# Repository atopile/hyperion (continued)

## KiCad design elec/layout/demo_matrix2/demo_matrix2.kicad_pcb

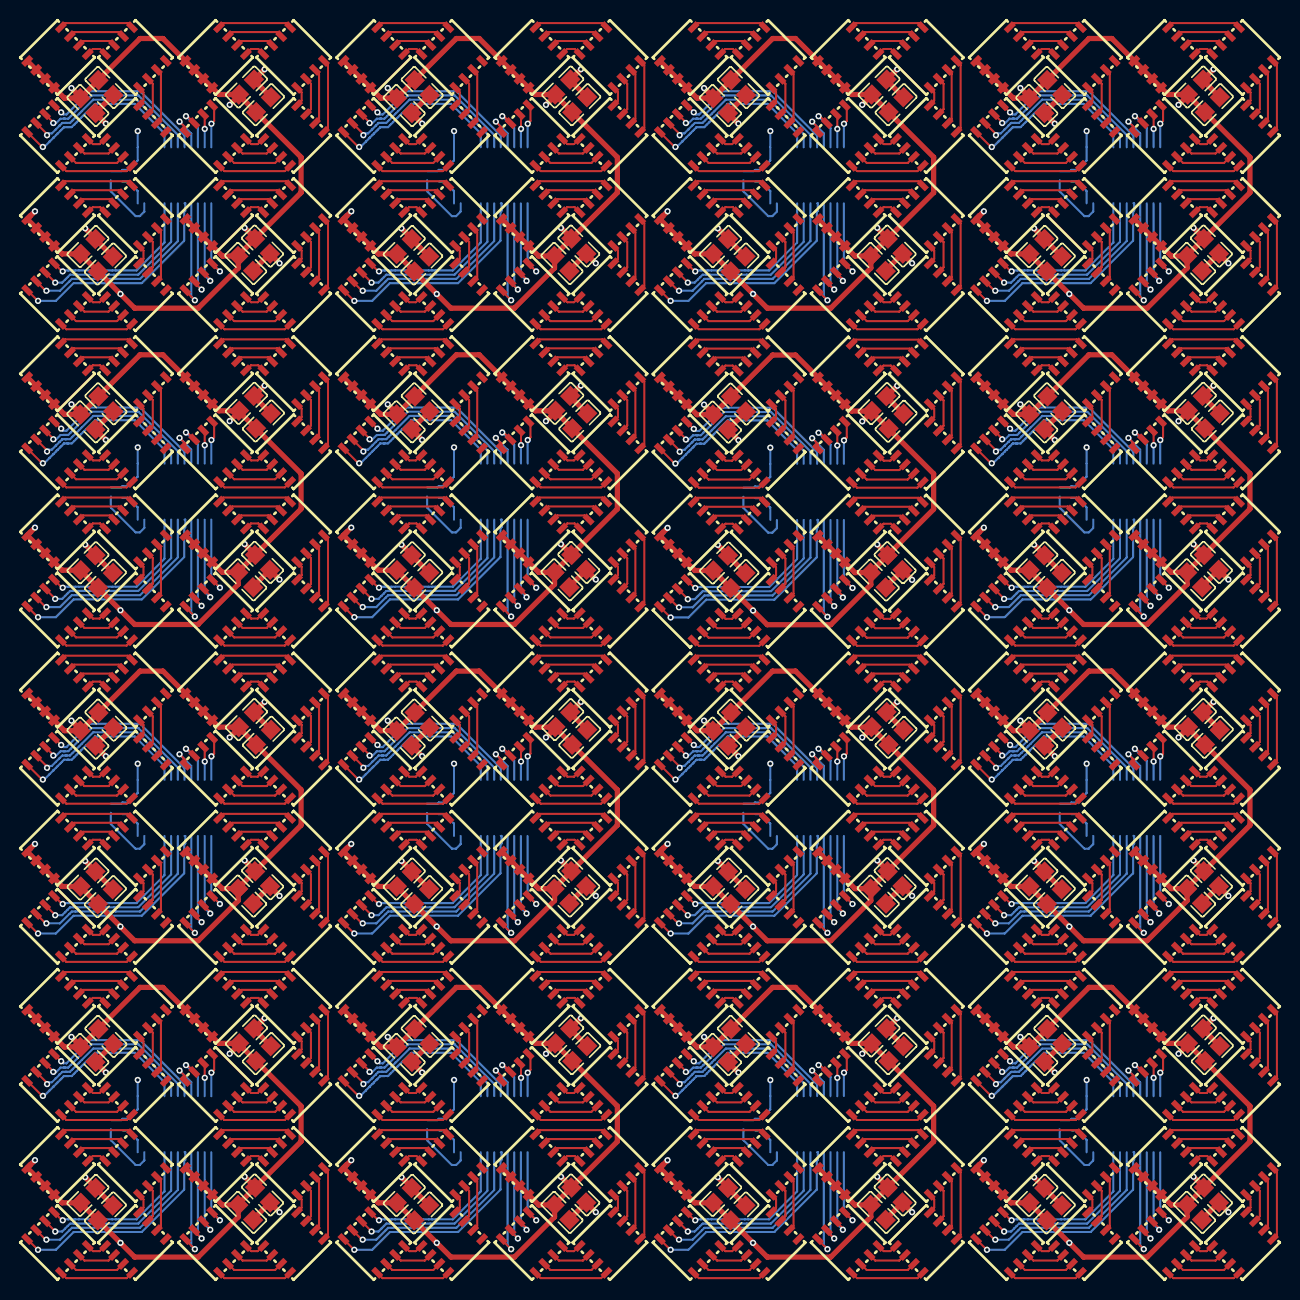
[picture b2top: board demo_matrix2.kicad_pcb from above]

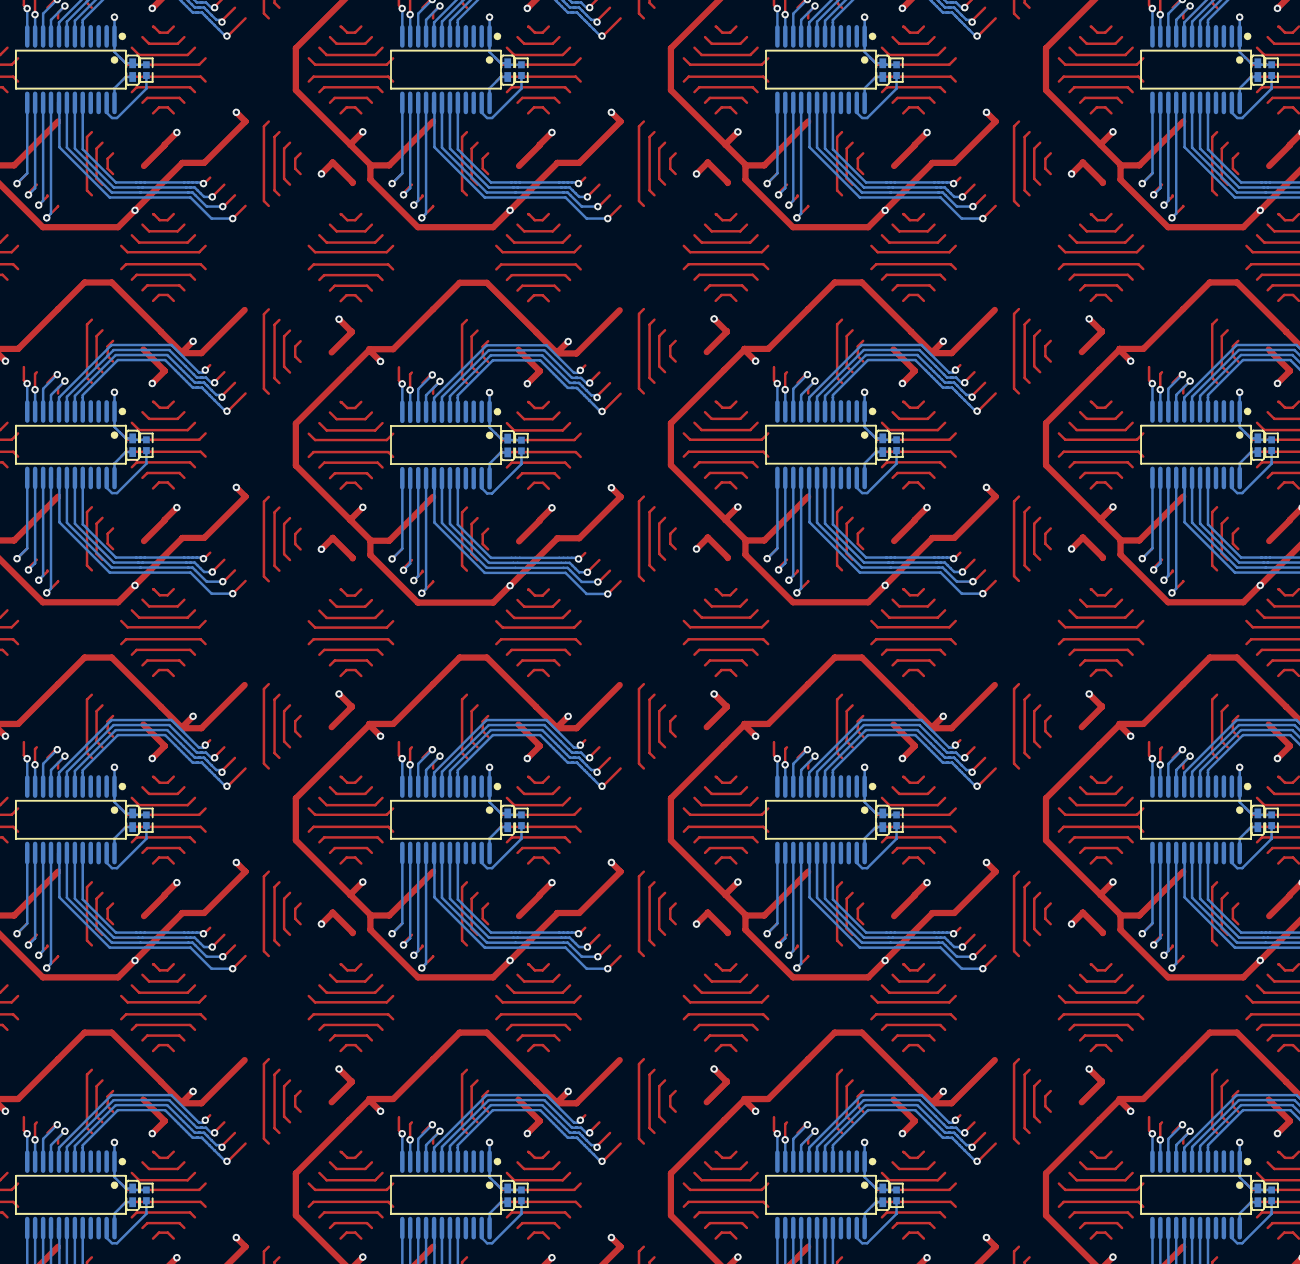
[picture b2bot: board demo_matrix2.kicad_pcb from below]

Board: 2 copper layers, 496 parts (48 on the bottom side), 1104 nets.

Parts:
C1, C2, C3, C4, C5, C6, C7, C8, C10, C11, C12, C13, C14, C15, C16, C17, C19, C20, C21, C22, C23, C24, C25, C26, C28, C29, C30, C31, C32, C33, C34, C35, C37, C38, C39, C40, C41, C42, C43, C44, C46, C47, C48, C49, C50, C51, C52, C53, C55, C56, C57, C58, C59, C60, C61, C62, C64, C65, C66, C67, C68, C69, C70, C71, C73, C74, C75, C76, C77, C78, C79, C80, C82, C83, C84, C85, C86, C87, C88, C89, C91, C92, C93, C94, C95, C96, C97, C98, C100, C101, C102, C103, C104, C105, C106, C107, C109, C110, C111, C112, C113, C114, C115, C116, C118, C119, C120, C121, C122, C123, C124, C125, C127, C128, C129, C130, C131, C132, C133, C134, C136, C137, C138, C139, C140, C141, C142, C143: 10µF ±10% 25V X5R; C0805
C9, C18, C27, C36, C45, C54, C63, C72, C81, C90, C99, C108, C117, C126, C135, C144: 100nF ±10% 16V X7R; C0402
LED1, LED2, LED3, LED4, LED5, LED6, LED7, LED8, LED9, LED10, LED11, LED12, LED13, LED14, LED15, LED16, LED17, LED18, LED19, LED20, LED21, LED22, LED23, LED24, LED25, LED26, LED27, LED28, LED29, LED30, LED31, LED32, LED33, LED34, LED35, LED36, LED37, LED38, LED39, LED40, LED41, LED42, LED43, LED44, LED45, LED46, LED47, LED48, LED49, LED50, LED51, LED52, LED53, LED54, LED55, LED56, LED57, LED58, LED59, LED60, LED61, LED62, LED63, LED64, LED65, LED66, LED67, LED68, LED69, LED70, LED71, LED72, LED73, LED74, LED75, LED76, LED77, LED78, LED79, LED80, LED81, LED82, LED83, LED84, LED85, LED86, LED87, LED88, LED89, LED90, LED91, LED92, LED93, LED94, LED95, LED96, LED97, LED98, LED99, LED100, LED101, LED102, LED103, LED104, LED105, LED106, LED107, LED108, LED109, LED110, LED111, LED112, LED113, LED114, LED115, LED116, LED117, LED118, LED119, LED120, LED121, LED122, LED123, LED124, LED125, LED126, LED127, LED128, LED129, LED130, LED131, LED132, LED133, LED134, LED135, LED136, LED137, LED138, LED139, LED140, LED141, LED142, LED143, LED144, LED145, LED146, LED147, LED148, LED149, LED150, LED151, LED152, LED153, LED154, LED155, LED156, LED157, LED158, LED159, LED160, LED161, LED162, LED163, LED164, LED165, LED166, LED167, LED168, LED169, LED170, LED171, LED172, LED173, LED174, LED175, LED176, LED177, LED178, LED179, LED180, LED181, LED182, LED183, LED184, LED185, LED186, LED187, LED188, LED189, LED190, LED191, LED192, LED193, LED194, LED195, LED196, LED197, LED198, LED199, LED200, LED201, LED202, LED203, LED204, LED205, LED206, LED207, LED208, LED209, LED210, LED211, LED212, LED213, LED214, LED215, LED216, LED217, LED218, LED219, LED220, LED221, LED222, LED223, LED224, LED225, LED226, LED227, LED228, LED229, LED230, LED231, LED232, LED233, LED234, LED235, LED236, LED237, LED238, LED239, LED240, LED241, LED242, LED243, LED244, LED245, LED246, LED247, LED248, LED249, LED250, LED251, LED252, LED253, LED254, LED255, LED256: LED-SMD_8P-L5.0-W5.0-P1.20_HL-5050RGBW-S1-A27
R1, R2, R3, R4, R5, R6, R7, R8, R9, R10, R11, R12, R13, R14, R15, R16: 10kΩ ±1% 62.5mW; R0402
U1, U6, U11, U16, U21, U26, U31, U36, U41, U46, U51, U56, U61, U66, U71, U76: SSOP-24_L8.8-W4.0-P0.64-LS6.2-BL
U2, U3, U4, U5, U7, U8, U9, U10, U12, U13, U14, U15, U17, U18, U19, U20, U22, U23, U24, U25, U27, U28, U29, U30, U32, U33, U34, U35, U37, U38, U39, U40, U42, U43, U44, U45, U47, U48, U49, U50, U52, U53, U54, U55, U57, U58, U59, U60, U62, U63, U64, U65, U67, U68, U69, U70, U72, U73, U74, U75, U77, U78, U79, U80: pixel15

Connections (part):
clusters[0]-REXT: R1.1, U1.23
clusters[1]-REXT: R2.1, U6.23
clusters[2]-REXT: R3.1, U11.23
clusters[3]-REXT: R4.1, U16.23
clusters[4]-REXT: R5.1, U21.23
clusters[5]-REXT: R6.1, U26.23
clusters[6]-REXT: R7.1, U31.23
clusters[7]-REXT: R8.1, U36.23
clusters[8]-REXT: R9.1, U41.23
clusters[9]-REXT: R10.1, U46.23
clusters[10]-REXT: R11.1, U51.23
clusters[11]-REXT: R12.1, U56.23
clusters[12]-REXT: R13.1, U61.23
clusters[13]-REXT: R14.1, U66.23
clusters[14]-REXT: R15.1, U71.23
clusters[15]-REXT: R16.1, U76.23
decoupling_capacitors[7]-power_shim-GND-0: C1.2, C2.2, C3.2, C4.2, C5.2, C6.2, C7.2, C8.2
decoupling_capacitors[7]-power_shim-GND-1: C91.2, C92.2, C93.2, C94.2, C95.2, C96.2, C97.2, C98.2
decoupling_capacitors[7]-power_shim-GND-2: C100.2, C101.2, C102.2, C103.2, C104.2, C105.2, C106.2, C107.2
decoupling_capacitors[7]-power_shim-GND-3: C109.2, C110.2, C111.2, C112.2, C113.2, C114.2, C115.2, C116.2
decoupling_capacitors[7]-power_shim-GND-4: C118.2, C119.2, C120.2, C121.2, C122.2, C123.2, C124.2, C125.2
decoupling_capacitors[7]-power_shim-GND-5: C127.2, C128.2, C129.2, C130.2, C131.2, C132.2, C133.2, C134.2
decoupling_capacitors[7]-power_shim-GND-6: C136.2, C137.2, C138.2, C139.2, C140.2, C141.2, C142.2, C143.2
decoupling_capacitors[7]-power_shim-GND-7: C10.2, C11.2, C12.2, C13.2, C14.2, C15.2, C16.2, C17.2
decoupling_capacitors[7]-power_shim-GND-8: C19.2, C20.2, C21.2, C22.2, C23.2, C24.2, C25.2, C26.2
decoupling_capacitors[7]-power_shim-GND-9: C28.2, C29.2, C30.2, C31.2, C32.2, C33.2, C34.2, C35.2
decoupling_capacitors[7]-power_shim-GND-10: C37.2, C38.2, C39.2, C40.2, C41.2, C42.2, C43.2, C44.2
decoupling_capacitors[7]-power_shim-GND-11: C46.2, C47.2, C48.2, C49.2, C50.2, C51.2, C52.2, C53.2
decoupling_capacitors[7]-power_shim-GND-12: C55.2, C56.2, C57.2, C58.2, C59.2, C60.2, C61.2, C62.2
decoupling_capacitors[7]-power_shim-GND-13: C64.2, C65.2, C66.2, C67.2, C68.2, C69.2, C70.2, C71.2
decoupling_capacitors[7]-power_shim-GND-14: C73.2, C74.2, C75.2, C76.2, C77.2, C78.2, C79.2, C80.2
decoupling_capacitors[7]-power_shim-GND-15: C82.2, C83.2, C84.2, C85.2, C86.2, C87.2, C88.2, C89.2
decoupling_capacitors[7]-power_shim-VCC-0: C1.1, C2.1, C3.1, C4.1, C5.1, C6.1, C7.1, C8.1, LED1.2, LED1.4, LED1.6, LED1.8, LED5.2, LED5.4, LED5.6, LED5.8, LED9.2, LED9.4, LED9.6, LED9.8, LED13.2, LED13.4, LED13.6, LED13.8
decoupling_capacitors[7]-power_shim-VCC-1: C91.1, C92.1, C93.1, C94.1, C95.1, C96.1, C97.1, C98.1, LED161.2, LED161.4, LED161.6, LED161.8, LED165.2, LED165.4, LED165.6, LED165.8, LED169.2, LED169.4, LED169.6, LED169.8, LED173.2, LED173.4, LED173.6, LED173.8
decoupling_capacitors[7]-power_shim-VCC-2: C100.1, C101.1, C102.1, C103.1, C104.1, C105.1, C106.1, C107.1, LED177.2, LED177.4, LED177.6, LED177.8, LED181.2, LED181.4, LED181.6, LED181.8, LED185.2, LED185.4, LED185.6, LED185.8, LED189.2, LED189.4, LED189.6, LED189.8
decoupling_capacitors[7]-power_shim-VCC-3: C109.1, C110.1, C111.1, C112.1, C113.1, C114.1, C115.1, C116.1, LED193.2, LED193.4, LED193.6, LED193.8, LED197.2, LED197.4, LED197.6, LED197.8, LED201.2, LED201.4, LED201.6, LED201.8, LED205.2, LED205.4, LED205.6, LED205.8
decoupling_capacitors[7]-power_shim-VCC-4: C118.1, C119.1, C120.1, C121.1, C122.1, C123.1, C124.1, C125.1, LED209.2, LED209.4, LED209.6, LED209.8, LED213.2, LED213.4, LED213.6, LED213.8, LED217.2, LED217.4, LED217.6, LED217.8, LED221.2, LED221.4, LED221.6, LED221.8
decoupling_capacitors[7]-power_shim-VCC-5: C127.1, C128.1, C129.1, C130.1, C131.1, C132.1, C133.1, C134.1, LED225.2, LED225.4, LED225.6, LED225.8, LED229.2, LED229.4, LED229.6, LED229.8, LED233.2, LED233.4, LED233.6, LED233.8, LED237.2, LED237.4, LED237.6, LED237.8
decoupling_capacitors[7]-power_shim-VCC-6: C136.1, C137.1, C138.1, C139.1, C140.1, C141.1, C142.1, C143.1, LED241.2, LED241.4, LED241.6, LED241.8, LED245.2, LED245.4, LED245.6, LED245.8, LED249.2, LED249.4, LED249.6, LED249.8, LED253.2, LED253.4, LED253.6, LED253.8
decoupling_capacitors[7]-power_shim-VCC-7: C10.1, C11.1, C12.1, C13.1, C14.1, C15.1, C16.1, C17.1, LED17.2, LED17.4, LED17.6, LED17.8, LED21.2, LED21.4, LED21.6, LED21.8, LED25.2, LED25.4, LED25.6, LED25.8, LED29.2, LED29.4, LED29.6, LED29.8
decoupling_capacitors[7]-power_shim-VCC-8: C19.1, C20.1, C21.1, C22.1, C23.1, C24.1, C25.1, C26.1, LED33.2, LED33.4, LED33.6, LED33.8, LED37.2, LED37.4, LED37.6, LED37.8, LED41.2, LED41.4, LED41.6, LED41.8, LED45.2, LED45.4, LED45.6, LED45.8
decoupling_capacitors[7]-power_shim-VCC-9: C28.1, C29.1, C30.1, C31.1, C32.1, C33.1, C34.1, C35.1, LED49.2, LED49.4, LED49.6, LED49.8, LED53.2, LED53.4, LED53.6, LED53.8, LED57.2, LED57.4, LED57.6, LED57.8, LED61.2, LED61.4, LED61.6, LED61.8
decoupling_capacitors[7]-power_shim-VCC-10: C37.1, C38.1, C39.1, C40.1, C41.1, C42.1, C43.1, C44.1, LED65.2, LED65.4, LED65.6, LED65.8, LED69.2, LED69.4, LED69.6, LED69.8, LED73.2, LED73.4, LED73.6, LED73.8, LED77.2, LED77.4, LED77.6, LED77.8
decoupling_capacitors[7]-power_shim-VCC-11: C46.1, C47.1, C48.1, C49.1, C50.1, C51.1, C52.1, C53.1, LED81.2, LED81.4, LED81.6, LED81.8, LED85.2, LED85.4, LED85.6, LED85.8, LED89.2, LED89.4, LED89.6, LED89.8, LED93.2, LED93.4, LED93.6, LED93.8
decoupling_capacitors[7]-power_shim-VCC-12: C55.1, C56.1, C57.1, C58.1, C59.1, C60.1, C61.1, C62.1, LED97.2, LED97.4, LED97.6, LED97.8, LED101.2, LED101.4, LED101.6, LED101.8, LED105.2, LED105.4, LED105.6, LED105.8, LED109.2, LED109.4, LED109.6, LED109.8
decoupling_capacitors[7]-power_shim-VCC-13: C64.1, C65.1, C66.1, C67.1, C68.1, C69.1, C70.1, C71.1, LED113.2, LED113.4, LED113.6, LED113.8, LED117.2, LED117.4, LED117.6, LED117.8, LED121.2, LED121.4, LED121.6, LED121.8, LED125.2, LED125.4, LED125.6, LED125.8
decoupling_capacitors[7]-power_shim-VCC-14: C73.1, C74.1, C75.1, C76.1, C77.1, C78.1, C79.1, C80.1, LED129.2, LED129.4, LED129.6, LED129.8, LED133.2, LED133.4, LED133.6, LED133.8, LED137.2, LED137.4, LED137.6, LED137.8, LED141.2, LED141.4, LED141.6, LED141.8
decoupling_capacitors[7]-power_shim-VCC-15: C82.1, C83.1, C84.1, C85.1, C86.1, C87.1, C88.1, C89.1, LED145.2, LED145.4, LED145.6, LED145.8, LED149.2, LED149.4, LED149.6, LED149.8, LED153.2, LED153.4, LED153.6, LED153.8, LED157.2, LED157.4, LED157.6, LED157.8
driver-power-GND-0: C9.2, R1.2, U1.1
driver-power-GND-1: C99.2, R11.2, U51.1
driver-power-GND-2: C108.2, R12.2, U56.1
driver-power-GND-3: C117.2, R13.2, U61.1
driver-power-GND-4: C126.2, R14.2, U66.1
driver-power-GND-5: C135.2, R15.2, U71.1
driver-power-GND-6: C144.2, R16.2, U76.1
driver-power-GND-7: C18.2, R2.2, U6.1
driver-power-GND-8: C27.2, R3.2, U11.1
driver-power-GND-9: C36.2, R4.2, U16.1
driver-power-GND-10: C45.2, R5.2, U21.1
driver-power-GND-11: C54.2, R6.2, U26.1
driver-power-GND-12: C63.2, R7.2, U31.1
driver-power-GND-13: C72.2, R8.2, U36.1
driver-power-GND-14: C81.2, R9.2, U41.1
driver-power-GND-15: C90.2, R10.2, U46.1
driver-power-VCC-0: C9.1, U1.24
driver-power-VCC-1: C99.1, U51.24
driver-power-VCC-2: C108.1, U56.24
driver-power-VCC-3: C117.1, U61.24
driver-power-VCC-4: C126.1, U66.24
driver-power-VCC-5: C135.1, U71.24
driver-power-VCC-6: C144.1, U76.24
driver-power-VCC-7: C18.1, U6.24
driver-power-VCC-8: C27.1, U11.24
driver-power-VCC-9: C36.1, U16.24
driver-power-VCC-10: C45.1, U21.24
driver-power-VCC-11: C54.1, U26.24
driver-power-VCC-12: C63.1, U31.24
driver-power-VCC-13: C72.1, U36.24
driver-power-VCC-14: C81.1, U41.24
driver-power-VCC-15: C90.1, U46.24
rgbs[1]-anodes-anode-0: LED1.3, LED2.4
rgbs[1]-anodes-anode-1: LED1.1, LED2.2
rgbs[1]-anodes-anode-2: LED1.5, LED2.6
rgbs[1]-anodes-anode-3: LED1.7, LED2.8
rgbs[1]-anodes-anode-4: LED5.3, LED6.4
rgbs[1]-anodes-anode-5: LED5.1, LED6.2
rgbs[1]-anodes-anode-6: LED5.5, LED6.6
rgbs[1]-anodes-anode-7: LED5.7, LED6.8
rgbs[1]-anodes-anode-8: LED9.3, LED10.4
rgbs[1]-anodes-anode-9: LED9.1, LED10.2
rgbs[1]-anodes-anode-10: LED9.5, LED10.6
rgbs[1]-anodes-anode-11: LED9.7, LED10.8
rgbs[1]-anodes-anode-12: LED13.3, LED14.4
rgbs[1]-anodes-anode-13: LED13.1, LED14.2
rgbs[1]-anodes-anode-14: LED13.5, LED14.6
rgbs[1]-anodes-anode-15: LED13.7, LED14.8
rgbs[1]-anodes-anode-16: LED161.3, LED162.4
rgbs[1]-anodes-anode-17: LED161.1, LED162.2
rgbs[1]-anodes-anode-18: LED161.5, LED162.6
rgbs[1]-anodes-anode-19: LED161.7, LED162.8
rgbs[1]-anodes-anode-20: LED165.3, LED166.4
rgbs[1]-anodes-anode-21: LED165.1, LED166.2
rgbs[1]-anodes-anode-22: LED165.5, LED166.6
rgbs[1]-anodes-anode-23: LED165.7, LED166.8
rgbs[1]-anodes-anode-24: LED169.3, LED170.4
rgbs[1]-anodes-anode-25: LED169.1, LED170.2
rgbs[1]-anodes-anode-26: LED169.5, LED170.6
rgbs[1]-anodes-anode-27: LED169.7, LED170.8
rgbs[1]-anodes-anode-28: LED173.3, LED174.4
rgbs[1]-anodes-anode-29: LED173.1, LED174.2
rgbs[1]-anodes-anode-30: LED173.5, LED174.6
rgbs[1]-anodes-anode-31: LED173.7, LED174.8
rgbs[1]-anodes-anode-32: LED177.3, LED178.4
rgbs[1]-anodes-anode-33: LED177.1, LED178.2
rgbs[1]-anodes-anode-34: LED177.5, LED178.6
rgbs[1]-anodes-anode-35: LED177.7, LED178.8
rgbs[1]-anodes-anode-36: LED181.3, LED182.4
rgbs[1]-anodes-anode-37: LED181.1, LED182.2
rgbs[1]-anodes-anode-38: LED181.5, LED182.6
rgbs[1]-anodes-anode-39: LED181.7, LED182.8
rgbs[1]-anodes-anode-40: LED185.3, LED186.4
rgbs[1]-anodes-anode-41: LED185.1, LED186.2
rgbs[1]-anodes-anode-42: LED185.5, LED186.6
rgbs[1]-anodes-anode-43: LED185.7, LED186.8
rgbs[1]-anodes-anode-44: LED189.3, LED190.4
rgbs[1]-anodes-anode-45: LED189.1, LED190.2
rgbs[1]-anodes-anode-46: LED189.5, LED190.6
rgbs[1]-anodes-anode-47: LED189.7, LED190.8
rgbs[1]-anodes-anode-48: LED193.3, LED194.4
rgbs[1]-anodes-anode-49: LED193.1, LED194.2
rgbs[1]-anodes-anode-50: LED193.5, LED194.6
rgbs[1]-anodes-anode-51: LED193.7, LED194.8
rgbs[1]-anodes-anode-52: LED197.3, LED198.4
rgbs[1]-anodes-anode-53: LED197.1, LED198.2
rgbs[1]-anodes-anode-54: LED197.5, LED198.6
rgbs[1]-anodes-anode-55: LED197.7, LED198.8
rgbs[1]-anodes-anode-56: LED201.3, LED202.4
rgbs[1]-anodes-anode-57: LED201.1, LED202.2
rgbs[1]-anodes-anode-58: LED201.5, LED202.6
rgbs[1]-anodes-anode-59: LED201.7, LED202.8
rgbs[1]-anodes-anode-60: LED205.3, LED206.4
rgbs[1]-anodes-anode-61: LED205.1, LED206.2
rgbs[1]-anodes-anode-62: LED205.5, LED206.6
rgbs[1]-anodes-anode-63: LED205.7, LED206.8
rgbs[1]-anodes-anode-64: LED209.3, LED210.4
rgbs[1]-anodes-anode-65: LED209.1, LED210.2
rgbs[1]-anodes-anode-66: LED209.5, LED210.6
rgbs[1]-anodes-anode-67: LED209.7, LED210.8
rgbs[1]-anodes-anode-68: LED213.3, LED214.4
rgbs[1]-anodes-anode-69: LED213.1, LED214.2
rgbs[1]-anodes-anode-70: LED213.5, LED214.6
rgbs[1]-anodes-anode-71: LED213.7, LED214.8
rgbs[1]-anodes-anode-72: LED217.3, LED218.4
rgbs[1]-anodes-anode-73: LED217.1, LED218.2
rgbs[1]-anodes-anode-74: LED217.5, LED218.6
rgbs[1]-anodes-anode-75: LED217.7, LED218.8
rgbs[1]-anodes-anode-76: LED221.3, LED222.4
rgbs[1]-anodes-anode-77: LED221.1, LED222.2
rgbs[1]-anodes-anode-78: LED221.5, LED222.6
rgbs[1]-anodes-anode-79: LED221.7, LED222.8
rgbs[1]-anodes-anode-80: LED225.3, LED226.4
rgbs[1]-anodes-anode-81: LED225.1, LED226.2
rgbs[1]-anodes-anode-82: LED225.5, LED226.6
rgbs[1]-anodes-anode-83: LED225.7, LED226.8
rgbs[1]-anodes-anode-84: LED229.3, LED230.4
rgbs[1]-anodes-anode-85: LED229.1, LED230.2
rgbs[1]-anodes-anode-86: LED229.5, LED230.6
rgbs[1]-anodes-anode-87: LED229.7, LED230.8
rgbs[1]-anodes-anode-88: LED233.3, LED234.4
rgbs[1]-anodes-anode-89: LED233.1, LED234.2
rgbs[1]-anodes-anode-90: LED233.5, LED234.6
rgbs[1]-anodes-anode-91: LED233.7, LED234.8
rgbs[1]-anodes-anode-92: LED237.3, LED238.4
rgbs[1]-anodes-anode-93: LED237.1, LED238.2
rgbs[1]-anodes-anode-94: LED237.5, LED238.6
rgbs[1]-anodes-anode-95: LED237.7, LED238.8
rgbs[1]-anodes-anode-96: LED241.3, LED242.4
rgbs[1]-anodes-anode-97: LED241.1, LED242.2
rgbs[1]-anodes-anode-98: LED241.5, LED242.6
rgbs[1]-anodes-anode-99: LED241.7, LED242.8
rgbs[1]-anodes-anode-100: LED245.3, LED246.4
rgbs[1]-anodes-anode-101: LED245.1, LED246.2
rgbs[1]-anodes-anode-102: LED245.5, LED246.6
rgbs[1]-anodes-anode-103: LED245.7, LED246.8
rgbs[1]-anodes-anode-104: LED249.3, LED250.4
rgbs[1]-anodes-anode-105: LED249.1, LED250.2
rgbs[1]-anodes-anode-106: LED249.5, LED250.6
rgbs[1]-anodes-anode-107: LED249.7, LED250.8
rgbs[1]-anodes-anode-108: LED253.3, LED254.4
rgbs[1]-anodes-anode-109: LED253.1, LED254.2
rgbs[1]-anodes-anode-110: LED253.5, LED254.6
rgbs[1]-anodes-anode-111: LED253.7, LED254.8
rgbs[1]-anodes-anode-112: LED17.3, LED18.4
rgbs[1]-anodes-anode-113: LED17.1, LED18.2
rgbs[1]-anodes-anode-114: LED17.5, LED18.6
rgbs[1]-anodes-anode-115: LED17.7, LED18.8
rgbs[1]-anodes-anode-116: LED21.3, LED22.4
rgbs[1]-anodes-anode-117: LED21.1, LED22.2
rgbs[1]-anodes-anode-118: LED21.5, LED22.6
rgbs[1]-anodes-anode-119: LED21.7, LED22.8
rgbs[1]-anodes-anode-120: LED25.3, LED26.4
rgbs[1]-anodes-anode-121: LED25.1, LED26.2
rgbs[1]-anodes-anode-122: LED25.5, LED26.6
rgbs[1]-anodes-anode-123: LED25.7, LED26.8
rgbs[1]-anodes-anode-124: LED29.3, LED30.4
rgbs[1]-anodes-anode-125: LED29.1, LED30.2
rgbs[1]-anodes-anode-126: LED29.5, LED30.6
rgbs[1]-anodes-anode-127: LED29.7, LED30.8
rgbs[1]-anodes-anode-128: LED33.3, LED34.4
rgbs[1]-anodes-anode-129: LED33.1, LED34.2
rgbs[1]-anodes-anode-130: LED33.5, LED34.6
rgbs[1]-anodes-anode-131: LED33.7, LED34.8
rgbs[1]-anodes-anode-132: LED37.3, LED38.4
rgbs[1]-anodes-anode-133: LED37.1, LED38.2
rgbs[1]-anodes-anode-134: LED37.5, LED38.6
rgbs[1]-anodes-anode-135: LED37.7, LED38.8
rgbs[1]-anodes-anode-136: LED41.3, LED42.4
rgbs[1]-anodes-anode-137: LED41.1, LED42.2
rgbs[1]-anodes-anode-138: LED41.5, LED42.6
rgbs[1]-anodes-anode-139: LED41.7, LED42.8
rgbs[1]-anodes-anode-140: LED45.3, LED46.4
rgbs[1]-anodes-anode-141: LED45.1, LED46.2
rgbs[1]-anodes-anode-142: LED45.5, LED46.6
rgbs[1]-anodes-anode-143: LED45.7, LED46.8
rgbs[1]-anodes-anode-144: LED49.3, LED50.4
rgbs[1]-anodes-anode-145: LED49.1, LED50.2
rgbs[1]-anodes-anode-146: LED49.5, LED50.6
rgbs[1]-anodes-anode-147: LED49.7, LED50.8
rgbs[1]-anodes-anode-148: LED53.3, LED54.4
rgbs[1]-anodes-anode-149: LED53.1, LED54.2
rgbs[1]-anodes-anode-150: LED53.5, LED54.6
rgbs[1]-anodes-anode-151: LED53.7, LED54.8
rgbs[1]-anodes-anode-152: LED57.3, LED58.4
rgbs[1]-anodes-anode-153: LED57.1, LED58.2
rgbs[1]-anodes-anode-154: LED57.5, LED58.6
rgbs[1]-anodes-anode-155: LED57.7, LED58.8
rgbs[1]-anodes-anode-156: LED61.3, LED62.4
rgbs[1]-anodes-anode-157: LED61.1, LED62.2
rgbs[1]-anodes-anode-158: LED61.5, LED62.6
rgbs[1]-anodes-anode-159: LED61.7, LED62.8
rgbs[1]-anodes-anode-160: LED65.3, LED66.4
rgbs[1]-anodes-anode-161: LED65.1, LED66.2
rgbs[1]-anodes-anode-162: LED65.5, LED66.6
rgbs[1]-anodes-anode-163: LED65.7, LED66.8
rgbs[1]-anodes-anode-164: LED69.3, LED70.4
rgbs[1]-anodes-anode-165: LED69.1, LED70.2
rgbs[1]-anodes-anode-166: LED69.5, LED70.6
rgbs[1]-anodes-anode-167: LED69.7, LED70.8
rgbs[1]-anodes-anode-168: LED73.3, LED74.4
rgbs[1]-anodes-anode-169: LED73.1, LED74.2
rgbs[1]-anodes-anode-170: LED73.5, LED74.6
rgbs[1]-anodes-anode-171: LED73.7, LED74.8
rgbs[1]-anodes-anode-172: LED77.3, LED78.4
rgbs[1]-anodes-anode-173: LED77.1, LED78.2
rgbs[1]-anodes-anode-174: LED77.5, LED78.6
rgbs[1]-anodes-anode-175: LED77.7, LED78.8
rgbs[1]-anodes-anode-176: LED81.3, LED82.4
rgbs[1]-anodes-anode-177: LED81.1, LED82.2
rgbs[1]-anodes-anode-178: LED81.5, LED82.6
rgbs[1]-anodes-anode-179: LED81.7, LED82.8
rgbs[1]-anodes-anode-180: LED85.3, LED86.4
rgbs[1]-anodes-anode-181: LED85.1, LED86.2
rgbs[1]-anodes-anode-182: LED85.5, LED86.6
rgbs[1]-anodes-anode-183: LED85.7, LED86.8
rgbs[1]-anodes-anode-184: LED89.3, LED90.4
rgbs[1]-anodes-anode-185: LED89.1, LED90.2
rgbs[1]-anodes-anode-186: LED89.5, LED90.6
rgbs[1]-anodes-anode-187: LED89.7, LED90.8
rgbs[1]-anodes-anode-188: LED93.3, LED94.4
rgbs[1]-anodes-anode-189: LED93.1, LED94.2
rgbs[1]-anodes-anode-190: LED93.5, LED94.6
rgbs[1]-anodes-anode-191: LED93.7, LED94.8
rgbs[1]-anodes-anode-192: LED97.3, LED98.4
rgbs[1]-anodes-anode-193: LED97.1, LED98.2
rgbs[1]-anodes-anode-194: LED97.5, LED98.6
rgbs[1]-anodes-anode-195: LED97.7, LED98.8
rgbs[1]-anodes-anode-196: LED101.3, LED102.4
rgbs[1]-anodes-anode-197: LED101.1, LED102.2
rgbs[1]-anodes-anode-198: LED101.5, LED102.6
rgbs[1]-anodes-anode-199: LED101.7, LED102.8
rgbs[1]-anodes-anode-200: LED105.3, LED106.4
rgbs[1]-anodes-anode-201: LED105.1, LED106.2
rgbs[1]-anodes-anode-202: LED105.5, LED106.6
rgbs[1]-anodes-anode-203: LED105.7, LED106.8
rgbs[1]-anodes-anode-204: LED109.3, LED110.4
rgbs[1]-anodes-anode-205: LED109.1, LED110.2
rgbs[1]-anodes-anode-206: LED109.5, LED110.6
rgbs[1]-anodes-anode-207: LED109.7, LED110.8
rgbs[1]-anodes-anode-208: LED113.3, LED114.4
rgbs[1]-anodes-anode-209: LED113.1, LED114.2
rgbs[1]-anodes-anode-210: LED113.5, LED114.6
rgbs[1]-anodes-anode-211: LED113.7, LED114.8
rgbs[1]-anodes-anode-212: LED117.3, LED118.4
rgbs[1]-anodes-anode-213: LED117.1, LED118.2
rgbs[1]-anodes-anode-214: LED117.5, LED118.6
rgbs[1]-anodes-anode-215: LED117.7, LED118.8
rgbs[1]-anodes-anode-216: LED121.3, LED122.4
rgbs[1]-anodes-anode-217: LED121.1, LED122.2
rgbs[1]-anodes-anode-218: LED121.5, LED122.6
rgbs[1]-anodes-anode-219: LED121.7, LED122.8
rgbs[1]-anodes-anode-220: LED125.3, LED126.4
rgbs[1]-anodes-anode-221: LED125.1, LED126.2
rgbs[1]-anodes-anode-222: LED125.5, LED126.6
rgbs[1]-anodes-anode-223: LED125.7, LED126.8
rgbs[1]-anodes-anode-224: LED129.3, LED130.4
rgbs[1]-anodes-anode-225: LED129.1, LED130.2
rgbs[1]-anodes-anode-226: LED129.5, LED130.6
rgbs[1]-anodes-anode-227: LED129.7, LED130.8
rgbs[1]-anodes-anode-228: LED133.3, LED134.4
rgbs[1]-anodes-anode-229: LED133.1, LED134.2
rgbs[1]-anodes-anode-230: LED133.5, LED134.6
rgbs[1]-anodes-anode-231: LED133.7, LED134.8
rgbs[1]-anodes-anode-232: LED137.3, LED138.4
rgbs[1]-anodes-anode-233: LED137.1, LED138.2
rgbs[1]-anodes-anode-234: LED137.5, LED138.6
rgbs[1]-anodes-anode-235: LED137.7, LED138.8
rgbs[1]-anodes-anode-236: LED141.3, LED142.4
rgbs[1]-anodes-anode-237: LED141.1, LED142.2
rgbs[1]-anodes-anode-238: LED141.5, LED142.6
rgbs[1]-anodes-anode-239: LED141.7, LED142.8
rgbs[1]-anodes-anode-240: LED145.3, LED146.4
rgbs[1]-anodes-anode-241: LED145.1, LED146.2
rgbs[1]-anodes-anode-242: LED145.5, LED146.6
rgbs[1]-anodes-anode-243: LED145.7, LED146.8
rgbs[1]-anodes-anode-244: LED149.3, LED150.4
rgbs[1]-anodes-anode-245: LED149.1, LED150.2
rgbs[1]-anodes-anode-246: LED149.5, LED150.6
rgbs[1]-anodes-anode-247: LED149.7, LED150.8
rgbs[1]-anodes-anode-248: LED153.3, LED154.4
rgbs[1]-anodes-anode-249: LED153.1, LED154.2
rgbs[1]-anodes-anode-250: LED153.5, LED154.6
rgbs[1]-anodes-anode-251: LED153.7, LED154.8
rgbs[1]-anodes-anode-252: LED157.3, LED158.4
rgbs[1]-anodes-anode-253: LED157.1, LED158.2
rgbs[1]-anodes-anode-254: LED157.5, LED158.6
rgbs[1]-anodes-anode-255: LED157.7, LED158.8
rgbs[2]-anodes-anode-0: LED2.3, LED3.4
rgbs[2]-anodes-anode-1: LED2.1, LED3.2
rgbs[2]-anodes-anode-2: LED2.5, LED3.6
rgbs[2]-anodes-anode-3: LED2.7, LED3.8
rgbs[2]-anodes-anode-4: LED6.3, LED7.4
rgbs[2]-anodes-anode-5: LED6.1, LED7.2
rgbs[2]-anodes-anode-6: LED6.5, LED7.6
rgbs[2]-anodes-anode-7: LED6.7, LED7.8
rgbs[2]-anodes-anode-8: LED10.3, LED11.4
rgbs[2]-anodes-anode-9: LED10.1, LED11.2
rgbs[2]-anodes-anode-10: LED10.5, LED11.6
rgbs[2]-anodes-anode-11: LED10.7, LED11.8
rgbs[2]-anodes-anode-12: LED14.3, LED15.4
rgbs[2]-anodes-anode-13: LED14.1, LED15.2
rgbs[2]-anodes-anode-14: LED14.5, LED15.6
rgbs[2]-anodes-anode-15: LED14.7, LED15.8
rgbs[2]-anodes-anode-16: LED162.3, LED163.4
rgbs[2]-anodes-anode-17: LED162.1, LED163.2
rgbs[2]-anodes-anode-18: LED162.5, LED163.6
rgbs[2]-anodes-anode-19: LED162.7, LED163.8
rgbs[2]-anodes-anode-20: LED166.3, LED167.4
rgbs[2]-anodes-anode-21: LED166.1, LED167.2
rgbs[2]-anodes-anode-22: LED166.5, LED167.6
rgbs[2]-anodes-anode-23: LED166.7, LED167.8
rgbs[2]-anodes-anode-24: LED170.3, LED171.4
rgbs[2]-anodes-anode-25: LED170.1, LED171.2
rgbs[2]-anodes-anode-26: LED170.5, LED171.6
rgbs[2]-anodes-anode-27: LED170.7, LED171.8
rgbs[2]-anodes-anode-28: LED174.3, LED175.4
rgbs[2]-anodes-anode-29: LED174.1, LED175.2
rgbs[2]-anodes-anode-30: LED174.5, LED175.6
rgbs[2]-anodes-anode-31: LED174.7, LED175.8
rgbs[2]-anodes-anode-32: LED178.3, LED179.4
rgbs[2]-anodes-anode-33: LED178.1, LED179.2
rgbs[2]-anodes-anode-34: LED178.5, LED179.6
rgbs[2]-anodes-anode-35: LED178.7, LED179.8
rgbs[2]-anodes-anode-36: LED182.3, LED183.4
rgbs[2]-anodes-anode-37: LED182.1, LED183.2
rgbs[2]-anodes-anode-38: LED182.5, LED183.6
rgbs[2]-anodes-anode-39: LED182.7, LED183.8
rgbs[2]-anodes-anode-40: LED186.3, LED187.4
rgbs[2]-anodes-anode-41: LED186.1, LED187.2
rgbs[2]-anodes-anode-42: LED186.5, LED187.6
rgbs[2]-anodes-anode-43: LED186.7, LED187.8
rgbs[2]-anodes-anode-44: LED190.3, LED191.4
rgbs[2]-anodes-anode-45: LED190.1, LED191.2
rgbs[2]-anodes-anode-46: LED190.5, LED191.6
rgbs[2]-anodes-anode-47: LED190.7, LED191.8
rgbs[2]-anodes-anode-48: LED194.3, LED195.4
rgbs[2]-anodes-anode-49: LED194.1, LED195.2
rgbs[2]-anodes-anode-50: LED194.5, LED195.6
rgbs[2]-anodes-anode-51: LED194.7, LED195.8
rgbs[2]-anodes-anode-52: LED198.3, LED199.4
rgbs[2]-anodes-anode-53: LED198.1, LED199.2
rgbs[2]-anodes-anode-54: LED198.5, LED199.6
rgbs[2]-anodes-anode-55: LED198.7, LED199.8
rgbs[2]-anodes-anode-56: LED202.3, LED203.4
rgbs[2]-anodes-anode-57: LED202.1, LED203.2
rgbs[2]-anodes-anode-58: LED202.5, LED203.6
rgbs[2]-anodes-anode-59: LED202.7, LED203.8
rgbs[2]-anodes-anode-60: LED206.3, LED207.4
rgbs[2]-anodes-anode-61: LED206.1, LED207.2
rgbs[2]-anodes-anode-62: LED206.5, LED207.6
rgbs[2]-anodes-anode-63: LED206.7, LED207.8
rgbs[2]-anodes-anode-64: LED210.3, LED211.4
rgbs[2]-anodes-anode-65: LED210.1, LED211.2
rgbs[2]-anodes-anode-66: LED210.5, LED211.6
rgbs[2]-anodes-anode-67: LED210.7, LED211.8
rgbs[2]-anodes-anode-68: LED214.3, LED215.4
rgbs[2]-anodes-anode-69: LED214.1, LED215.2
rgbs[2]-anodes-anode-70: LED214.5, LED215.6
rgbs[2]-anodes-anode-71: LED214.7, LED215.8
rgbs[2]-anodes-anode-72: LED218.3, LED219.4
rgbs[2]-anodes-anode-73: LED218.1, LED219.2
rgbs[2]-anodes-anode-74: LED218.5, LED219.6
rgbs[2]-anodes-anode-75: LED218.7, LED219.8
rgbs[2]-anodes-anode-76: LED222.3, LED223.4
rgbs[2]-anodes-anode-77: LED222.1, LED223.2
rgbs[2]-anodes-anode-78: LED222.5, LED223.6
rgbs[2]-anodes-anode-79: LED222.7, LED223.8
rgbs[2]-anodes-anode-80: LED226.3, LED227.4
rgbs[2]-anodes-anode-81: LED226.1, LED227.2
rgbs[2]-anodes-anode-82: LED226.5, LED227.6
rgbs[2]-anodes-anode-83: LED226.7, LED227.8
rgbs[2]-anodes-anode-84: LED230.3, LED231.4
rgbs[2]-anodes-anode-85: LED230.1, LED231.2
rgbs[2]-anodes-anode-86: LED230.5, LED231.6
rgbs[2]-anodes-anode-87: LED230.7, LED231.8
rgbs[2]-anodes-anode-88: LED234.3, LED235.4
rgbs[2]-anodes-anode-89: LED234.1, LED235.2
rgbs[2]-anodes-anode-90: LED234.5, LED235.6
rgbs[2]-anodes-anode-91: LED234.7, LED235.8
rgbs[2]-anodes-anode-92: LED238.3, LED239.4
rgbs[2]-anodes-anode-93: LED238.1, LED239.2
rgbs[2]-anodes-anode-94: LED238.5, LED239.6
rgbs[2]-anodes-anode-95: LED238.7, LED239.8
rgbs[2]-anodes-anode-96: LED242.3, LED243.4
rgbs[2]-anodes-anode-97: LED242.1, LED243.2
rgbs[2]-anodes-anode-98: LED242.5, LED243.6
rgbs[2]-anodes-anode-99: LED242.7, LED243.8
rgbs[2]-anodes-anode-100: LED246.3, LED247.4
rgbs[2]-anodes-anode-101: LED246.1, LED247.2
rgbs[2]-anodes-anode-102: LED246.5, LED247.6
rgbs[2]-anodes-anode-103: LED246.7, LED247.8
rgbs[2]-anodes-anode-104: LED250.3, LED251.4
rgbs[2]-anodes-anode-105: LED250.1, LED251.2
rgbs[2]-anodes-anode-106: LED250.5, LED251.6
rgbs[2]-anodes-anode-107: LED250.7, LED251.8
rgbs[2]-anodes-anode-108: LED254.3, LED255.4
rgbs[2]-anodes-anode-109: LED254.1, LED255.2
rgbs[2]-anodes-anode-110: LED254.5, LED255.6
rgbs[2]-anodes-anode-111: LED254.7, LED255.8
rgbs[2]-anodes-anode-112: LED18.3, LED19.4
rgbs[2]-anodes-anode-113: LED18.1, LED19.2
rgbs[2]-anodes-anode-114: LED18.5, LED19.6
rgbs[2]-anodes-anode-115: LED18.7, LED19.8
rgbs[2]-anodes-anode-116: LED22.3, LED23.4
rgbs[2]-anodes-anode-117: LED22.1, LED23.2
rgbs[2]-anodes-anode-118: LED22.5, LED23.6
rgbs[2]-anodes-anode-119: LED22.7, LED23.8
rgbs[2]-anodes-anode-120: LED26.3, LED27.4
rgbs[2]-anodes-anode-121: LED26.1, LED27.2
rgbs[2]-anodes-anode-122: LED26.5, LED27.6
rgbs[2]-anodes-anode-123: LED26.7, LED27.8
rgbs[2]-anodes-anode-124: LED30.3, LED31.4
rgbs[2]-anodes-anode-125: LED30.1, LED31.2
rgbs[2]-anodes-anode-126: LED30.5, LED31.6
rgbs[2]-anodes-anode-127: LED30.7, LED31.8
rgbs[2]-anodes-anode-128: LED34.3, LED35.4
rgbs[2]-anodes-anode-129: LED34.1, LED35.2
rgbs[2]-anodes-anode-130: LED34.5, LED35.6
rgbs[2]-anodes-anode-131: LED34.7, LED35.8
rgbs[2]-anodes-anode-132: LED38.3, LED39.4
rgbs[2]-anodes-anode-133: LED38.1, LED39.2
rgbs[2]-anodes-anode-134: LED38.5, LED39.6
rgbs[2]-anodes-anode-135: LED38.7, LED39.8
rgbs[2]-anodes-anode-136: LED42.3, LED43.4
rgbs[2]-anodes-anode-137: LED42.1, LED43.2
rgbs[2]-anodes-anode-138: LED42.5, LED43.6
rgbs[2]-anodes-anode-139: LED42.7, LED43.8
rgbs[2]-anodes-anode-140: LED46.3, LED47.4
rgbs[2]-anodes-anode-141: LED46.1, LED47.2
rgbs[2]-anodes-anode-142: LED46.5, LED47.6
rgbs[2]-anodes-anode-143: LED46.7, LED47.8
rgbs[2]-anodes-anode-144: LED50.3, LED51.4
rgbs[2]-anodes-anode-145: LED50.1, LED51.2
rgbs[2]-anodes-anode-146: LED50.5, LED51.6
rgbs[2]-anodes-anode-147: LED50.7, LED51.8
rgbs[2]-anodes-anode-148: LED54.3, LED55.4
rgbs[2]-anodes-anode-149: LED54.1, LED55.2
rgbs[2]-anodes-anode-150: LED54.5, LED55.6
rgbs[2]-anodes-anode-151: LED54.7, LED55.8
rgbs[2]-anodes-anode-152: LED58.3, LED59.4
rgbs[2]-anodes-anode-153: LED58.1, LED59.2
rgbs[2]-anodes-anode-154: LED58.5, LED59.6
rgbs[2]-anodes-anode-155: LED58.7, LED59.8
rgbs[2]-anodes-anode-156: LED62.3, LED63.4
rgbs[2]-anodes-anode-157: LED62.1, LED63.2
rgbs[2]-anodes-anode-158: LED62.5, LED63.6
rgbs[2]-anodes-anode-159: LED62.7, LED63.8
rgbs[2]-anodes-anode-160: LED66.3, LED67.4
rgbs[2]-anodes-anode-161: LED66.1, LED67.2
rgbs[2]-anodes-anode-162: LED66.5, LED67.6
rgbs[2]-anodes-anode-163: LED66.7, LED67.8
rgbs[2]-anodes-anode-164: LED70.3, LED71.4
rgbs[2]-anodes-anode-165: LED70.1, LED71.2
rgbs[2]-anodes-anode-166: LED70.5, LED71.6
rgbs[2]-anodes-anode-167: LED70.7, LED71.8
rgbs[2]-anodes-anode-168: LED74.3, LED75.4
rgbs[2]-anodes-anode-169: LED74.1, LED75.2
rgbs[2]-anodes-anode-170: LED74.5, LED75.6
rgbs[2]-anodes-anode-171: LED74.7, LED75.8
rgbs[2]-anodes-anode-172: LED78.3, LED79.4
rgbs[2]-anodes-anode-173: LED78.1, LED79.2
rgbs[2]-anodes-anode-174: LED78.5, LED79.6
rgbs[2]-anodes-anode-175: LED78.7, LED79.8
rgbs[2]-anodes-anode-176: LED82.3, LED83.4
rgbs[2]-anodes-anode-177: LED82.1, LED83.2
rgbs[2]-anodes-anode-178: LED82.5, LED83.6
rgbs[2]-anodes-anode-179: LED82.7, LED83.8
rgbs[2]-anodes-anode-180: LED86.3, LED87.4
rgbs[2]-anodes-anode-181: LED86.1, LED87.2
rgbs[2]-anodes-anode-182: LED86.5, LED87.6
rgbs[2]-anodes-anode-183: LED86.7, LED87.8
rgbs[2]-anodes-anode-184: LED90.3, LED91.4
rgbs[2]-anodes-anode-185: LED90.1, LED91.2
rgbs[2]-anodes-anode-186: LED90.5, LED91.6
rgbs[2]-anodes-anode-187: LED90.7, LED91.8
rgbs[2]-anodes-anode-188: LED94.3, LED95.4
rgbs[2]-anodes-anode-189: LED94.1, LED95.2
rgbs[2]-anodes-anode-190: LED94.5, LED95.6
rgbs[2]-anodes-anode-191: LED94.7, LED95.8
rgbs[2]-anodes-anode-192: LED98.3, LED99.4
rgbs[2]-anodes-anode-193: LED98.1, LED99.2
rgbs[2]-anodes-anode-194: LED98.5, LED99.6
rgbs[2]-anodes-anode-195: LED98.7, LED99.8
rgbs[2]-anodes-anode-196: LED102.3, LED103.4
rgbs[2]-anodes-anode-197: LED102.1, LED103.2
rgbs[2]-anodes-anode-198: LED102.5, LED103.6
rgbs[2]-anodes-anode-199: LED102.7, LED103.8
rgbs[2]-anodes-anode-200: LED106.3, LED107.4
rgbs[2]-anodes-anode-201: LED106.1, LED107.2
rgbs[2]-anodes-anode-202: LED106.5, LED107.6
rgbs[2]-anodes-anode-203: LED106.7, LED107.8
rgbs[2]-anodes-anode-204: LED110.3, LED111.4
rgbs[2]-anodes-anode-205: LED110.1, LED111.2
rgbs[2]-anodes-anode-206: LED110.5, LED111.6
rgbs[2]-anodes-anode-207: LED110.7, LED111.8
rgbs[2]-anodes-anode-208: LED114.3, LED115.4
rgbs[2]-anodes-anode-209: LED114.1, LED115.2
rgbs[2]-anodes-anode-210: LED114.5, LED115.6
rgbs[2]-anodes-anode-211: LED114.7, LED115.8
rgbs[2]-anodes-anode-212: LED118.3, LED119.4
rgbs[2]-anodes-anode-213: LED118.1, LED119.2
rgbs[2]-anodes-anode-214: LED118.5, LED119.6
rgbs[2]-anodes-anode-215: LED118.7, LED119.8
rgbs[2]-anodes-anode-216: LED122.3, LED123.4
rgbs[2]-anodes-anode-217: LED122.1, LED123.2
rgbs[2]-anodes-anode-218: LED122.5, LED123.6
rgbs[2]-anodes-anode-219: LED122.7, LED123.8
rgbs[2]-anodes-anode-220: LED126.3, LED127.4
rgbs[2]-anodes-anode-221: LED126.1, LED127.2
rgbs[2]-anodes-anode-222: LED126.5, LED127.6
rgbs[2]-anodes-anode-223: LED126.7, LED127.8
rgbs[2]-anodes-anode-224: LED130.3, LED131.4
rgbs[2]-anodes-anode-225: LED130.1, LED131.2
rgbs[2]-anodes-anode-226: LED130.5, LED131.6
rgbs[2]-anodes-anode-227: LED130.7, LED131.8
rgbs[2]-anodes-anode-228: LED134.3, LED135.4
rgbs[2]-anodes-anode-229: LED134.1, LED135.2
rgbs[2]-anodes-anode-230: LED134.5, LED135.6
rgbs[2]-anodes-anode-231: LED134.7, LED135.8
rgbs[2]-anodes-anode-232: LED138.3, LED139.4
rgbs[2]-anodes-anode-233: LED138.1, LED139.2
rgbs[2]-anodes-anode-234: LED138.5, LED139.6
rgbs[2]-anodes-anode-235: LED138.7, LED139.8
rgbs[2]-anodes-anode-236: LED142.3, LED143.4
rgbs[2]-anodes-anode-237: LED142.1, LED143.2
rgbs[2]-anodes-anode-238: LED142.5, LED143.6
rgbs[2]-anodes-anode-239: LED142.7, LED143.8
rgbs[2]-anodes-anode-240: LED146.3, LED147.4
rgbs[2]-anodes-anode-241: LED146.1, LED147.2
rgbs[2]-anodes-anode-242: LED146.5, LED147.6
rgbs[2]-anodes-anode-243: LED146.7, LED147.8
rgbs[2]-anodes-anode-244: LED150.3, LED151.4
rgbs[2]-anodes-anode-245: LED150.1, LED151.2
rgbs[2]-anodes-anode-246: LED150.5, LED151.6
rgbs[2]-anodes-anode-247: LED150.7, LED151.8
rgbs[2]-anodes-anode-248: LED154.3, LED155.4
rgbs[2]-anodes-anode-249: LED154.1, LED155.2
rgbs[2]-anodes-anode-250: LED154.5, LED155.6
rgbs[2]-anodes-anode-251: LED154.7, LED155.8
rgbs[2]-anodes-anode-252: LED158.3, LED159.4
rgbs[2]-anodes-anode-253: LED158.1, LED159.2
rgbs[2]-anodes-anode-254: LED158.5, LED159.6
rgbs[2]-anodes-anode-255: LED158.7, LED159.8
rgbs[3]-anodes-anode-0: LED3.3, LED4.4
rgbs[3]-anodes-anode-1: LED3.1, LED4.2
rgbs[3]-anodes-anode-2: LED3.5, LED4.6
rgbs[3]-anodes-anode-3: LED3.7, LED4.8
rgbs[3]-anodes-anode-4: LED7.3, LED8.4
rgbs[3]-anodes-anode-5: LED7.1, LED8.2
rgbs[3]-anodes-anode-6: LED7.5, LED8.6
rgbs[3]-anodes-anode-7: LED7.7, LED8.8
rgbs[3]-anodes-anode-8: LED11.3, LED12.4
rgbs[3]-anodes-anode-9: LED11.1, LED12.2
rgbs[3]-anodes-anode-10: LED11.5, LED12.6
rgbs[3]-anodes-anode-11: LED11.7, LED12.8
rgbs[3]-anodes-anode-12: LED15.3, LED16.4
rgbs[3]-anodes-anode-13: LED15.1, LED16.2
rgbs[3]-anodes-anode-14: LED15.5, LED16.6
rgbs[3]-anodes-anode-15: LED15.7, LED16.8
rgbs[3]-anodes-anode-16: LED163.3, LED164.4
rgbs[3]-anodes-anode-17: LED163.1, LED164.2
rgbs[3]-anodes-anode-18: LED163.5, LED164.6
rgbs[3]-anodes-anode-19: LED163.7, LED164.8
rgbs[3]-anodes-anode-20: LED167.3, LED168.4
rgbs[3]-anodes-anode-21: LED167.1, LED168.2
rgbs[3]-anodes-anode-22: LED167.5, LED168.6
rgbs[3]-anodes-anode-23: LED167.7, LED168.8
rgbs[3]-anodes-anode-24: LED171.3, LED172.4
rgbs[3]-anodes-anode-25: LED171.1, LED172.2
rgbs[3]-anodes-anode-26: LED171.5, LED172.6
rgbs[3]-anodes-anode-27: LED171.7, LED172.8
rgbs[3]-anodes-anode-28: LED175.3, LED176.4
rgbs[3]-anodes-anode-29: LED175.1, LED176.2
rgbs[3]-anodes-anode-30: LED175.5, LED176.6
rgbs[3]-anodes-anode-31: LED175.7, LED176.8
rgbs[3]-anodes-anode-32: LED179.3, LED180.4
rgbs[3]-anodes-anode-33: LED179.1, LED180.2
rgbs[3]-anodes-anode-34: LED179.5, LED180.6
rgbs[3]-anodes-anode-35: LED179.7, LED180.8
rgbs[3]-anodes-anode-36: LED183.3, LED184.4
rgbs[3]-anodes-anode-37: LED183.1, LED184.2
rgbs[3]-anodes-anode-38: LED183.5, LED184.6
rgbs[3]-anodes-anode-39: LED183.7, LED184.8
rgbs[3]-anodes-anode-40: LED187.3, LED188.4
rgbs[3]-anodes-anode-41: LED187.1, LED188.2
rgbs[3]-anodes-anode-42: LED187.5, LED188.6
rgbs[3]-anodes-anode-43: LED187.7, LED188.8
rgbs[3]-anodes-anode-44: LED191.3, LED192.4
rgbs[3]-anodes-anode-45: LED191.1, LED192.2
rgbs[3]-anodes-anode-46: LED191.5, LED192.6
rgbs[3]-anodes-anode-47: LED191.7, LED192.8
rgbs[3]-anodes-anode-48: LED195.3, LED196.4
rgbs[3]-anodes-anode-49: LED195.1, LED196.2
rgbs[3]-anodes-anode-50: LED195.5, LED196.6
rgbs[3]-anodes-anode-51: LED195.7, LED196.8
rgbs[3]-anodes-anode-52: LED199.3, LED200.4
rgbs[3]-anodes-anode-53: LED199.1, LED200.2
rgbs[3]-anodes-anode-54: LED199.5, LED200.6
rgbs[3]-anodes-anode-55: LED199.7, LED200.8
rgbs[3]-anodes-anode-56: LED203.3, LED204.4
rgbs[3]-anodes-anode-57: LED203.1, LED204.2
rgbs[3]-anodes-anode-58: LED203.5, LED204.6
rgbs[3]-anodes-anode-59: LED203.7, LED204.8
rgbs[3]-anodes-anode-60: LED207.3, LED208.4
rgbs[3]-anodes-anode-61: LED207.1, LED208.2
rgbs[3]-anodes-anode-62: LED207.5, LED208.6
rgbs[3]-anodes-anode-63: LED207.7, LED208.8
rgbs[3]-anodes-anode-64: LED211.3, LED212.4
rgbs[3]-anodes-anode-65: LED211.1, LED212.2
rgbs[3]-anodes-anode-66: LED211.5, LED212.6
rgbs[3]-anodes-anode-67: LED211.7, LED212.8
rgbs[3]-anodes-anode-68: LED215.3, LED216.4
rgbs[3]-anodes-anode-69: LED215.1, LED216.2
rgbs[3]-anodes-anode-70: LED215.5, LED216.6
rgbs[3]-anodes-anode-71: LED215.7, LED216.8
rgbs[3]-anodes-anode-72: LED219.3, LED220.4
rgbs[3]-anodes-anode-73: LED219.1, LED220.2
rgbs[3]-anodes-anode-74: LED219.5, LED220.6
rgbs[3]-anodes-anode-75: LED219.7, LED220.8
rgbs[3]-anodes-anode-76: LED223.3, LED224.4
rgbs[3]-anodes-anode-77: LED223.1, LED224.2
rgbs[3]-anodes-anode-78: LED223.5, LED224.6
rgbs[3]-anodes-anode-79: LED223.7, LED224.8
rgbs[3]-anodes-anode-80: LED227.3, LED228.4
rgbs[3]-anodes-anode-81: LED227.1, LED228.2
rgbs[3]-anodes-anode-82: LED227.5, LED228.6
rgbs[3]-anodes-anode-83: LED227.7, LED228.8
rgbs[3]-anodes-anode-84: LED231.3, LED232.4
rgbs[3]-anodes-anode-85: LED231.1, LED232.2
rgbs[3]-anodes-anode-86: LED231.5, LED232.6
rgbs[3]-anodes-anode-87: LED231.7, LED232.8
rgbs[3]-anodes-anode-88: LED235.3, LED236.4
rgbs[3]-anodes-anode-89: LED235.1, LED236.2
rgbs[3]-anodes-anode-90: LED235.5, LED236.6
rgbs[3]-anodes-anode-91: LED235.7, LED236.8
rgbs[3]-anodes-anode-92: LED239.3, LED240.4
rgbs[3]-anodes-anode-93: LED239.1, LED240.2
rgbs[3]-anodes-anode-94: LED239.5, LED240.6
rgbs[3]-anodes-anode-95: LED239.7, LED240.8
rgbs[3]-anodes-anode-96: LED243.3, LED244.4
rgbs[3]-anodes-anode-97: LED243.1, LED244.2
rgbs[3]-anodes-anode-98: LED243.5, LED244.6
rgbs[3]-anodes-anode-99: LED243.7, LED244.8
rgbs[3]-anodes-anode-100: LED247.3, LED248.4
rgbs[3]-anodes-anode-101: LED247.1, LED248.2
rgbs[3]-anodes-anode-102: LED247.5, LED248.6
rgbs[3]-anodes-anode-103: LED247.7, LED248.8
rgbs[3]-anodes-anode-104: LED251.3, LED252.4
rgbs[3]-anodes-anode-105: LED251.1, LED252.2
rgbs[3]-anodes-anode-106: LED251.5, LED252.6
rgbs[3]-anodes-anode-107: LED251.7, LED252.8
rgbs[3]-anodes-anode-108: LED255.3, LED256.4
rgbs[3]-anodes-anode-109: LED255.1, LED256.2
rgbs[3]-anodes-anode-110: LED255.5, LED256.6
rgbs[3]-anodes-anode-111: LED255.7, LED256.8
rgbs[3]-anodes-anode-112: LED19.3, LED20.4
rgbs[3]-anodes-anode-113: LED19.1, LED20.2
rgbs[3]-anodes-anode-114: LED19.5, LED20.6
rgbs[3]-anodes-anode-115: LED19.7, LED20.8
rgbs[3]-anodes-anode-116: LED23.3, LED24.4
rgbs[3]-anodes-anode-117: LED23.1, LED24.2
rgbs[3]-anodes-anode-118: LED23.5, LED24.6
rgbs[3]-anodes-anode-119: LED23.7, LED24.8
rgbs[3]-anodes-anode-120: LED27.3, LED28.4
rgbs[3]-anodes-anode-121: LED27.1, LED28.2
rgbs[3]-anodes-anode-122: LED27.5, LED28.6
rgbs[3]-anodes-anode-123: LED27.7, LED28.8
rgbs[3]-anodes-anode-124: LED31.3, LED32.4
rgbs[3]-anodes-anode-125: LED31.1, LED32.2
rgbs[3]-anodes-anode-126: LED31.5, LED32.6
rgbs[3]-anodes-anode-127: LED31.7, LED32.8
rgbs[3]-anodes-anode-128: LED35.3, LED36.4
rgbs[3]-anodes-anode-129: LED35.1, LED36.2
rgbs[3]-anodes-anode-130: LED35.5, LED36.6
rgbs[3]-anodes-anode-131: LED35.7, LED36.8
rgbs[3]-anodes-anode-132: LED39.3, LED40.4
rgbs[3]-anodes-anode-133: LED39.1, LED40.2
rgbs[3]-anodes-anode-134: LED39.5, LED40.6
rgbs[3]-anodes-anode-135: LED39.7, LED40.8
rgbs[3]-anodes-anode-136: LED43.3, LED44.4
rgbs[3]-anodes-anode-137: LED43.1, LED44.2
rgbs[3]-anodes-anode-138: LED43.5, LED44.6
rgbs[3]-anodes-anode-139: LED43.7, LED44.8
rgbs[3]-anodes-anode-140: LED47.3, LED48.4
rgbs[3]-anodes-anode-141: LED47.1, LED48.2
rgbs[3]-anodes-anode-142: LED47.5, LED48.6
rgbs[3]-anodes-anode-143: LED47.7, LED48.8
rgbs[3]-anodes-anode-144: LED51.3, LED52.4
rgbs[3]-anodes-anode-145: LED51.1, LED52.2
rgbs[3]-anodes-anode-146: LED51.5, LED52.6
rgbs[3]-anodes-anode-147: LED51.7, LED52.8
rgbs[3]-anodes-anode-148: LED55.3, LED56.4
rgbs[3]-anodes-anode-149: LED55.1, LED56.2
rgbs[3]-anodes-anode-150: LED55.5, LED56.6
rgbs[3]-anodes-anode-151: LED55.7, LED56.8
rgbs[3]-anodes-anode-152: LED59.3, LED60.4
rgbs[3]-anodes-anode-153: LED59.1, LED60.2
rgbs[3]-anodes-anode-154: LED59.5, LED60.6
rgbs[3]-anodes-anode-155: LED59.7, LED60.8
rgbs[3]-anodes-anode-156: LED63.3, LED64.4
rgbs[3]-anodes-anode-157: LED63.1, LED64.2
rgbs[3]-anodes-anode-158: LED63.5, LED64.6
rgbs[3]-anodes-anode-159: LED63.7, LED64.8
rgbs[3]-anodes-anode-160: LED67.3, LED68.4
rgbs[3]-anodes-anode-161: LED67.1, LED68.2
rgbs[3]-anodes-anode-162: LED67.5, LED68.6
rgbs[3]-anodes-anode-163: LED67.7, LED68.8
rgbs[3]-anodes-anode-164: LED71.3, LED72.4
rgbs[3]-anodes-anode-165: LED71.1, LED72.2
rgbs[3]-anodes-anode-166: LED71.5, LED72.6
rgbs[3]-anodes-anode-167: LED71.7, LED72.8
rgbs[3]-anodes-anode-168: LED75.3, LED76.4
rgbs[3]-anodes-anode-169: LED75.1, LED76.2
rgbs[3]-anodes-anode-170: LED75.5, LED76.6
rgbs[3]-anodes-anode-171: LED75.7, LED76.8
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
